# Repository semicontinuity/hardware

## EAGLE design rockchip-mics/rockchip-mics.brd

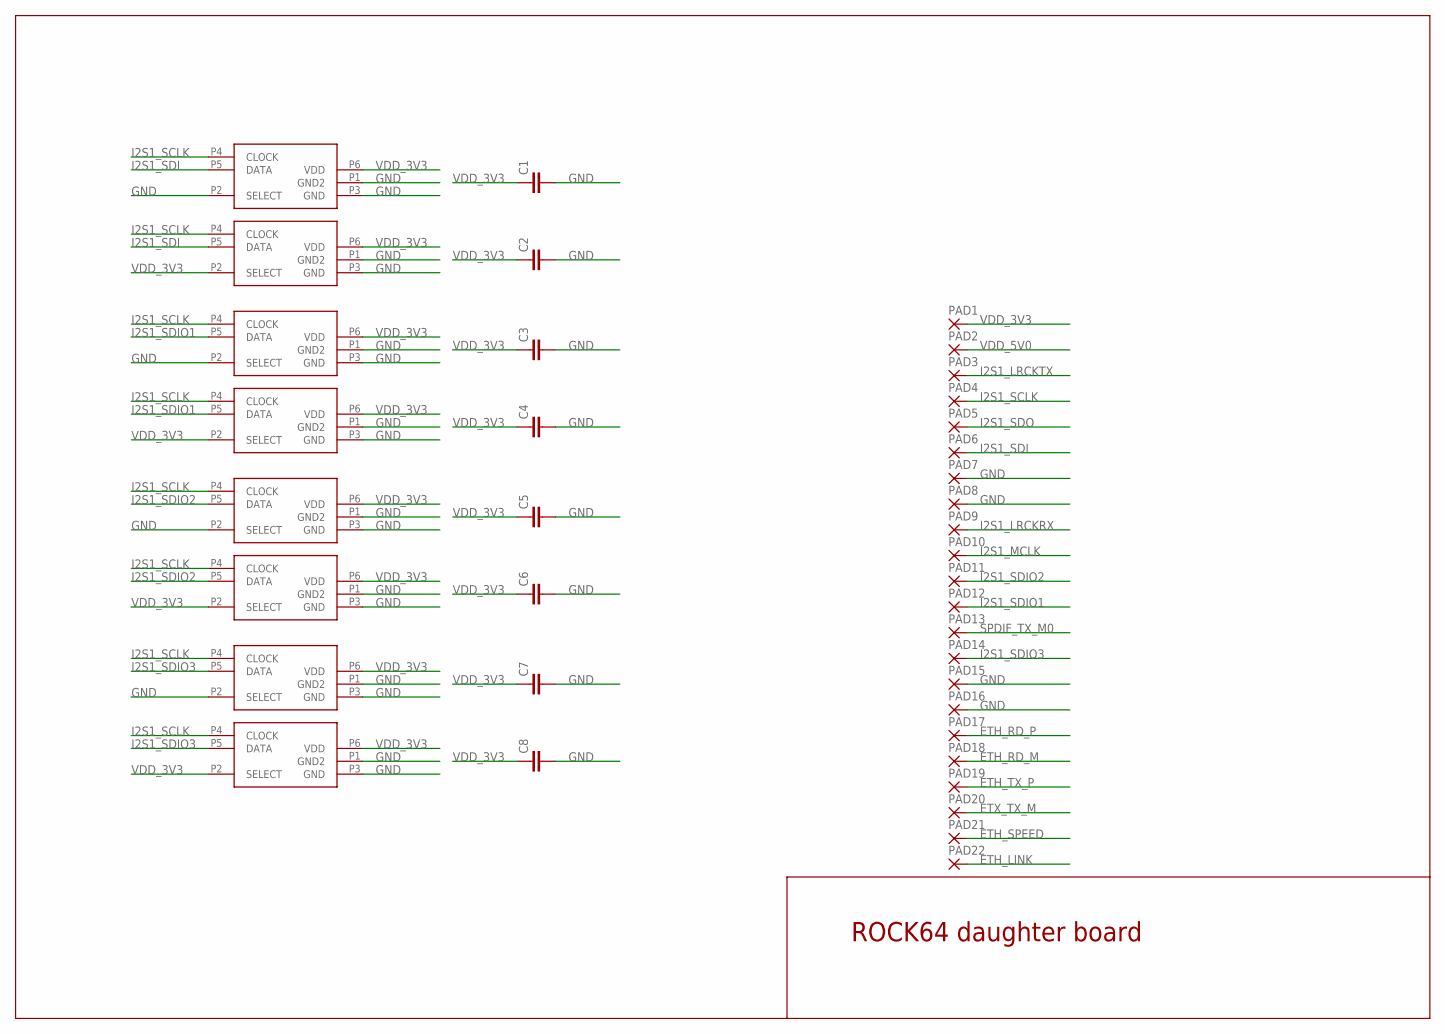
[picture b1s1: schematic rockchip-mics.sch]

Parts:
C1, C2, C3, C4, C5, C6, C7, C8: C-EUC1206; C1206
PAD1, PAD2, PAD3, PAD4, PAD5, PAD6, PAD7, PAD8, PAD9, PAD10, PAD11, PAD12, PAD13, PAD14, PAD15, PAD16, PAD17, PAD18, PAD19, PAD20, PAD21, PAD22: 1,6/0,8
U$1, U$2, U$3, U$4, U$5, U$6, U$7, U$8: SPM0423SMD; SPM0423

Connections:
ETH_LINK: PAD22.1
ETH_RD_M: PAD18.1
ETH_RD_P: PAD17.1
ETH_SPEED: PAD21.1
ETH_TX_P: PAD19.1
ETX_TX_M: PAD20.1
GND: C1.2, C2.2, C3.2, C4.2, C5.2, C6.2, C7.2, C8.2, PAD7.1, PAD8.1, PAD15.1, PAD16.1, U$1.P1 (GND2), U$1.P2 (SELECT), U$1.P3 (GND), U$2.P1 (GND2), U$2.P3 (GND), U$3.P1 (GND2), U$3.P2 (SELECT), U$3.P3 (GND), U$4.P1 (GND2), U$4.P3 (GND), U$5.P1 (GND2), U$5.P2 (SELECT), U$5.P3 (GND), U$6.P1 (GND2), U$6.P3 (GND), U$7.P1 (GND2), U$7.P2 (SELECT), U$7.P3 (GND), U$8.P1 (GND2), U$8.P3 (GND)
I2S1_LRCKRX: PAD9.1
I2S1_LRCKTX: PAD3.1
I2S1_MCLK: PAD10.1
I2S1_SCLK: PAD4.1, U$1.P4 (CLOCK), U$2.P4 (CLOCK), U$3.P4 (CLOCK), U$4.P4 (CLOCK), U$5.P4 (CLOCK), U$6.P4 (CLOCK), U$7.P4 (CLOCK), U$8.P4 (CLOCK)
I2S1_SDI: PAD6.1, U$1.P5 (DATA), U$2.P5 (DATA)
I2S1_SDIO1: PAD12.1, U$3.P5 (DATA), U$4.P5 (DATA)
I2S1_SDIO2: PAD11.1, U$5.P5 (DATA), U$6.P5 (DATA)
I2S1_SDIO3: PAD14.1, U$7.P5 (DATA), U$8.P5 (DATA)
I2S1_SDO: PAD5.1
SPDIF_TX_M0: PAD13.1
VDD_3V3: C1.1, C2.1, C3.1, C4.1, C5.1, C6.1, C7.1, C8.1, PAD1.1, U$1.P6 (VDD), U$2.P2 (SELECT), U$2.P6 (VDD), U$3.P6 (VDD), U$4.P2 (SELECT), U$4.P6 (VDD), U$5.P6 (VDD), U$6.P2 (SELECT), U$6.P6 (VDD), U$7.P6 (VDD), U$8.P2 (SELECT), U$8.P6 (VDD)
VDD_5V0: PAD2.1

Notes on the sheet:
ROCK64 daughter board

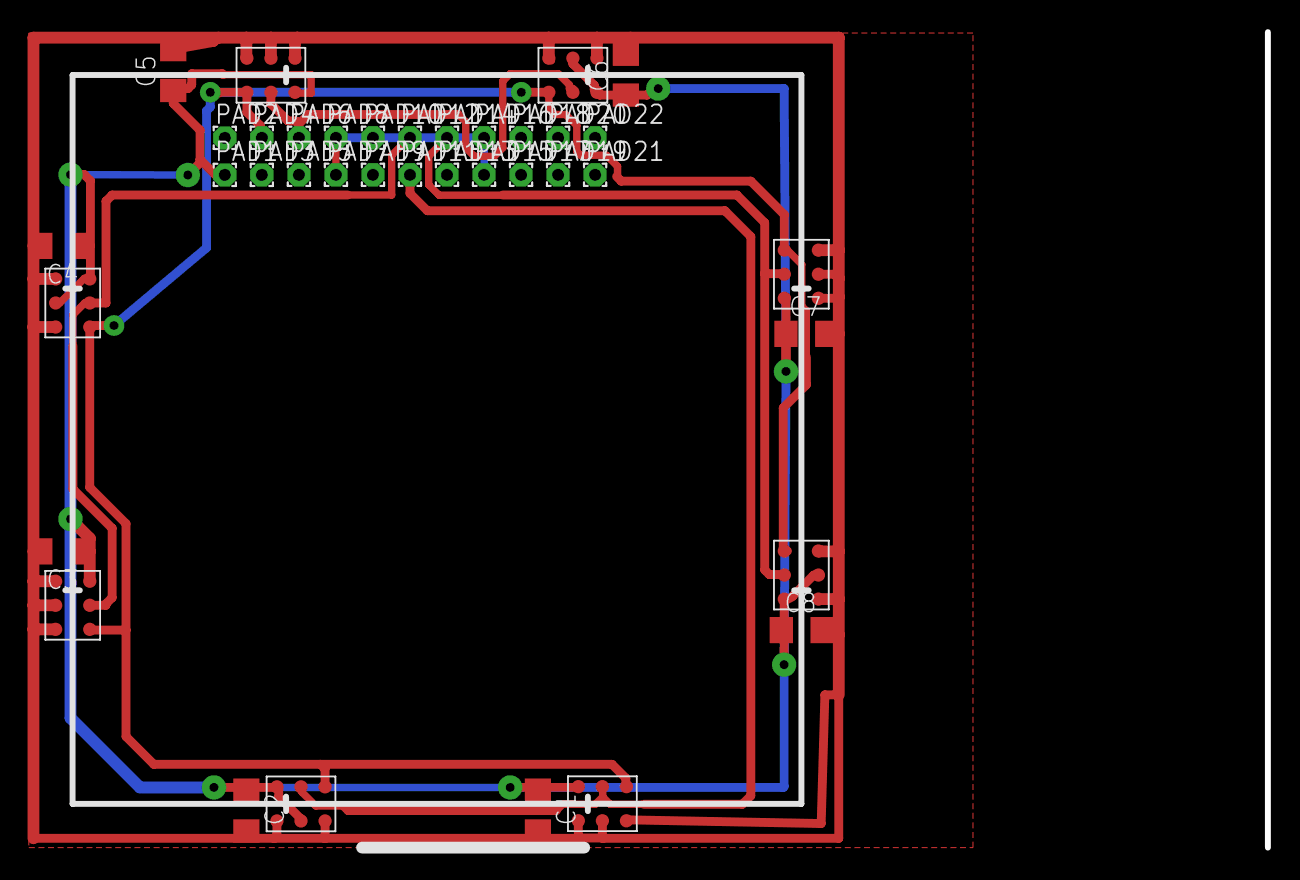
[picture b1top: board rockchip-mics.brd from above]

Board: 2 copper layers, 38 parts (0 on the bottom side), 7 nets.

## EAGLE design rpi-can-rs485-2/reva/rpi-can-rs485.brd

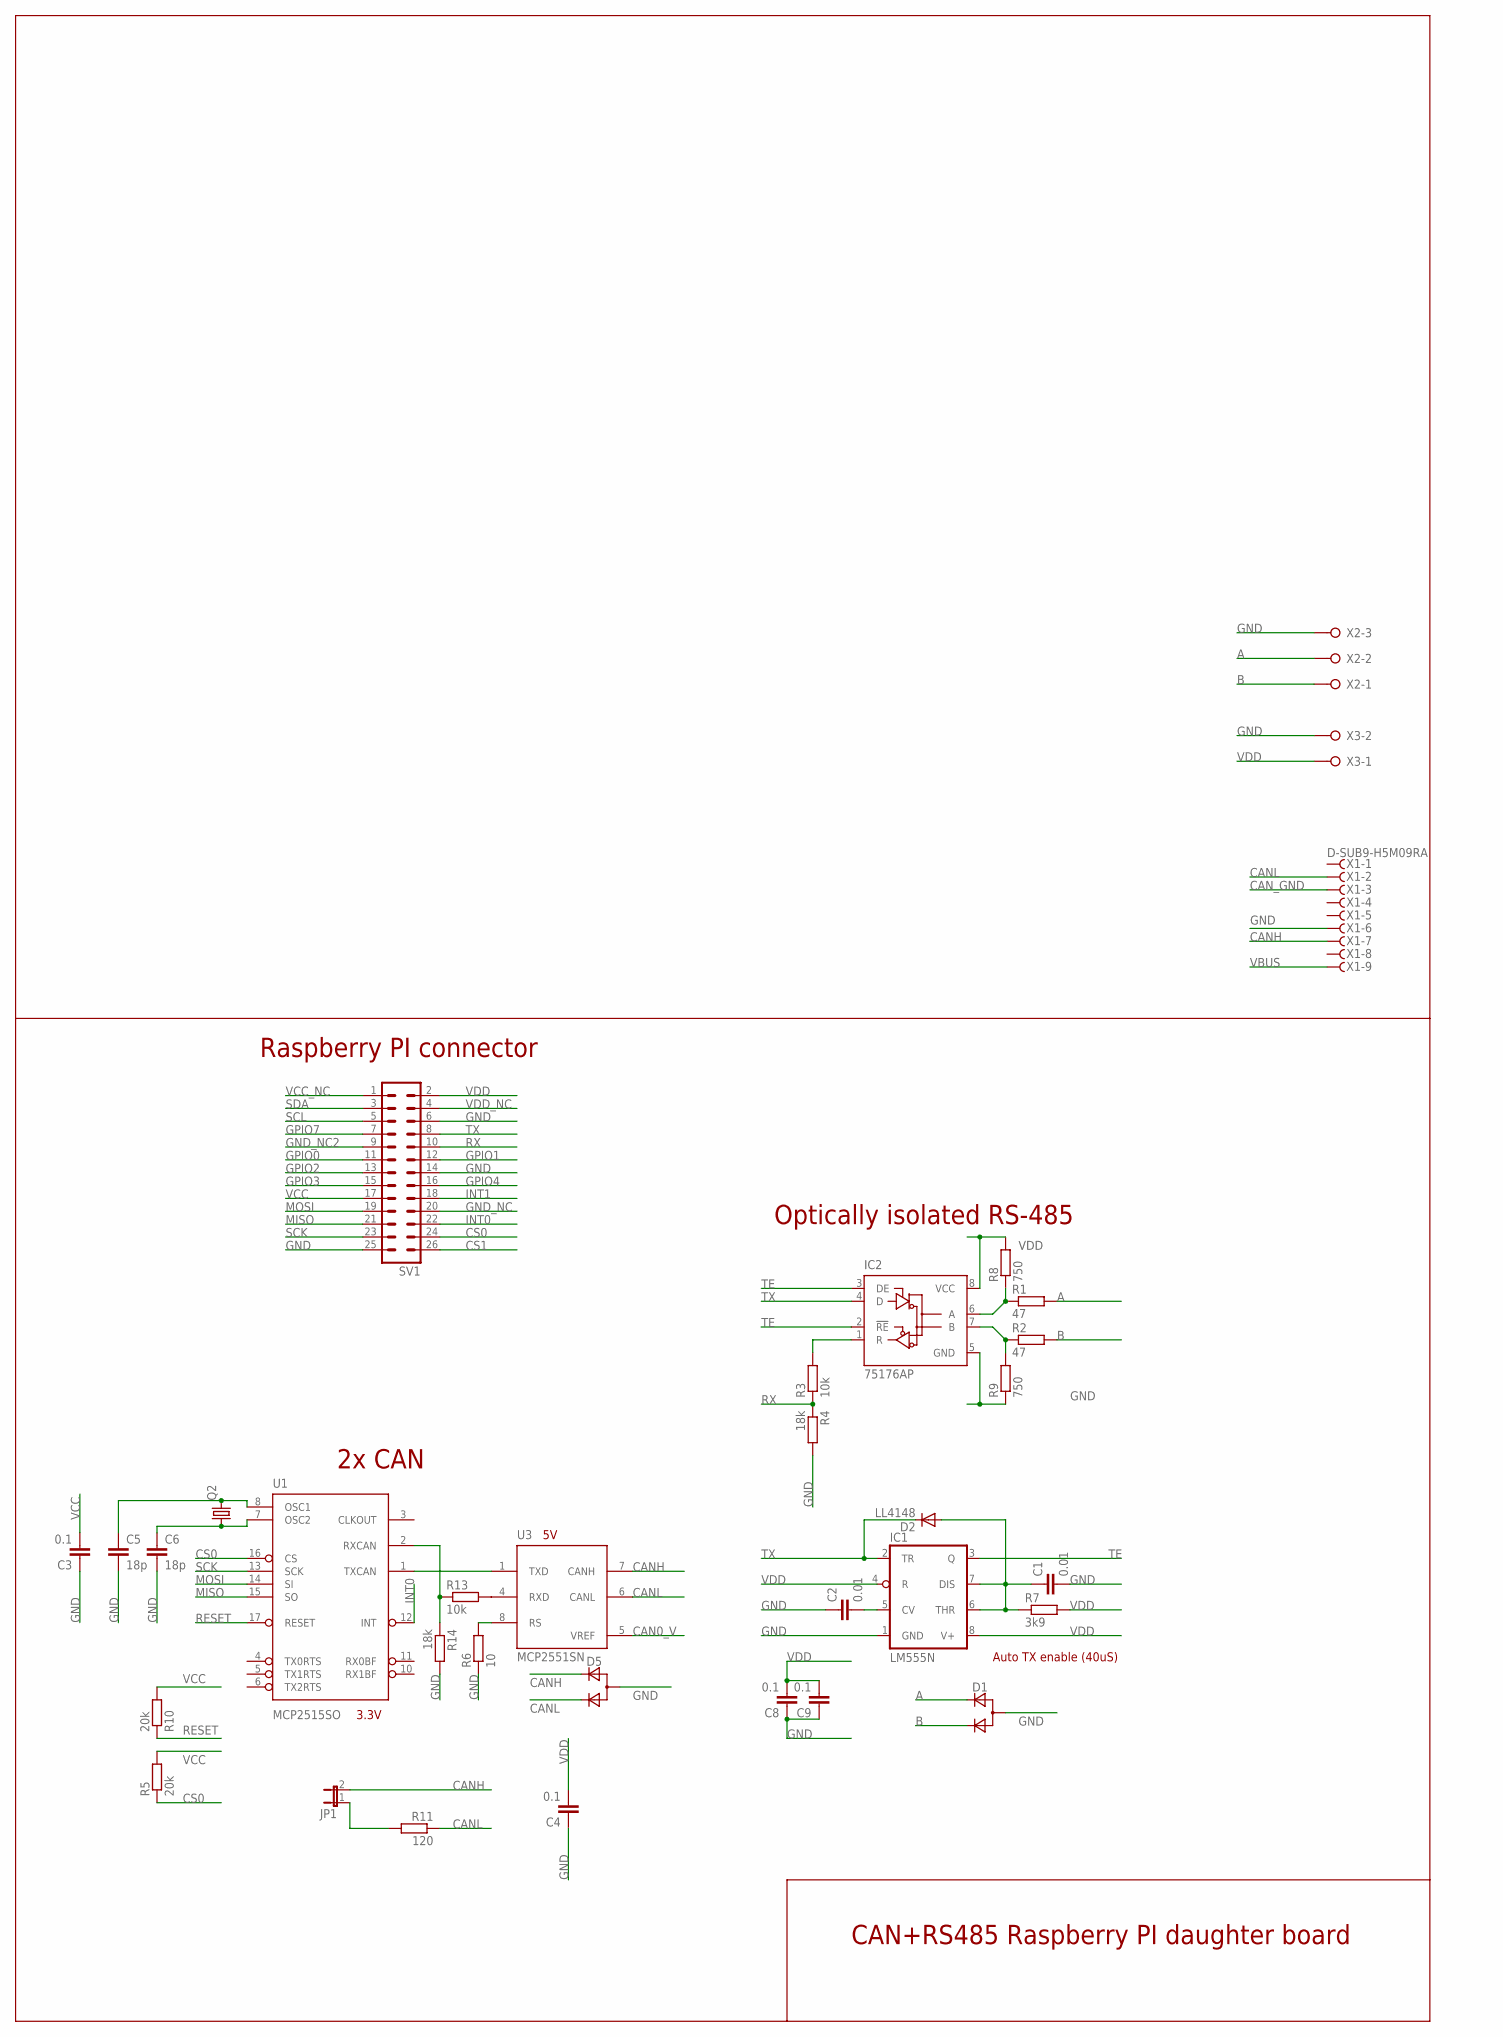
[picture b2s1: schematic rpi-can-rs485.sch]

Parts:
C1, C2: 0.01; C0805
C3, C4, C8, C9: 0.1; C0805
C5, C6: 18p; C0805
D1, D5: D_2CSOT323; SOT323
D2: LL4148; SOD80C
IC1: LM555N; DIL08
IC2: 75176AP; DIL08
JP1: JP1E; JP1
Q2: CRYSTALHC49S; HC49/S
R1, R2: 47; R1206
R3, R13: 10k; R0805
R4, R14: 18k; R0805
R5: 20k; R0603
R6: 10; R0805
R7: 3k9; R0805
R8, R9: 750; R1206
R10: 20k; R0805
R11: 120; R0805
SV1: MA13-2
U1: MCP2515SO; SO-18W
U3: MCP2551SN; SO-08
X1: D-SUB9-H5M09RA; H5M09RA
X2: W237-03P; W237-133
X3: W237-02P; W237-132

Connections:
A: D1.2 (C1), R1.2, X2.2
B: D1.3 (C2), R2.2, X2.1
CAN0_TX: U1.1 (TXCAN), U3.1 (TXD)
CAN0_V: U3.5 (VREF)
CANH: D5.2 (C1), JP1.2, U3.7 (CANH), X1.7
CANL: D5.3 (C2), R11.1, U3.6 (CANL), X1.2
CAN_GND: X1.3
CS0: R5.1, SV1.24, U1.16 (CS)
CS1: SV1.26
GND: C1.2, C2.1, C3.1, C4.1, C5.2, C6.2, C8.1, C9.1, D1.1 (A), D5.1 (A), IC1.1 (GND), IC2.5 (GND), R4.2, R6.1, R9.1, R14.2, SV1.6, SV1.14, SV1.25, U1.9 (VSS), U3.2 (VSS), X1.6, X2.3, X3.2
GND_NC: SV1.20
GND_NC2: SV1.9
GPIO0: SV1.11
GPIO1: SV1.12
GPIO2: SV1.13
GPIO3: SV1.15
GPIO4: SV1.16
GPIO7: SV1.7
INT0: SV1.22, U1.12 (INT)
INT1: SV1.18
MISO: SV1.21, U1.15 (SO)
MOSI: SV1.19, U1.14 (SI)
unnamed: C6.1, Q2.1, U1.7 (OSC2)
unnamed: C1.1, D2.A, IC1.6 (THR), IC1.7 (DIS), R7.1
unnamed: IC2.7 (B), R2.1, R9.2
unnamed: IC2.6 (A), R1.1, R8.1
unnamed: C2.2, IC1.5 (CV)
unnamed: C5.1, Q2.2, U1.8 (OSC1)
unnamed: R6.2, U3.8 (RS)
unnamed: IC2.1 (R), R3.2
unnamed: JP1.1, R11.2
unnamed: R13.2, U3.4 (RXD)
unnamed: R13.1, R14.1, U1.2 (RXCAN)
RESET: R10.1, U1.17 (RESET)
RX: R3.1, R4.1, SV1.10
SCK: SV1.23, U1.13 (SCK)
SCL: SV1.5
SDA: SV1.3
TE: IC1.3 (Q), IC2.2 (!RE), IC2.3 (DE)
TX: D2.C, IC1.2 (TR), IC2.4 (D), SV1.8
VBUS: X1.9
VCC: C3.2, R5.2, R10.2, SV1.17, U1.18 (VDD)
VCC_NC: SV1.1
VDD: C4.2, C8.2, C9.2, IC1.4 (R), IC1.8 (V+), IC2.8 (VCC), R7.2, R8.2, SV1.2, U3.3 (VDD), X3.1
VDD_NC: SV1.4

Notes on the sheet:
Raspberry PI connector
2x CAN
Optically isolated RS-485
Auto TX enable (40uS)
CAN+RS485 Raspberry PI daughter board
3.3V

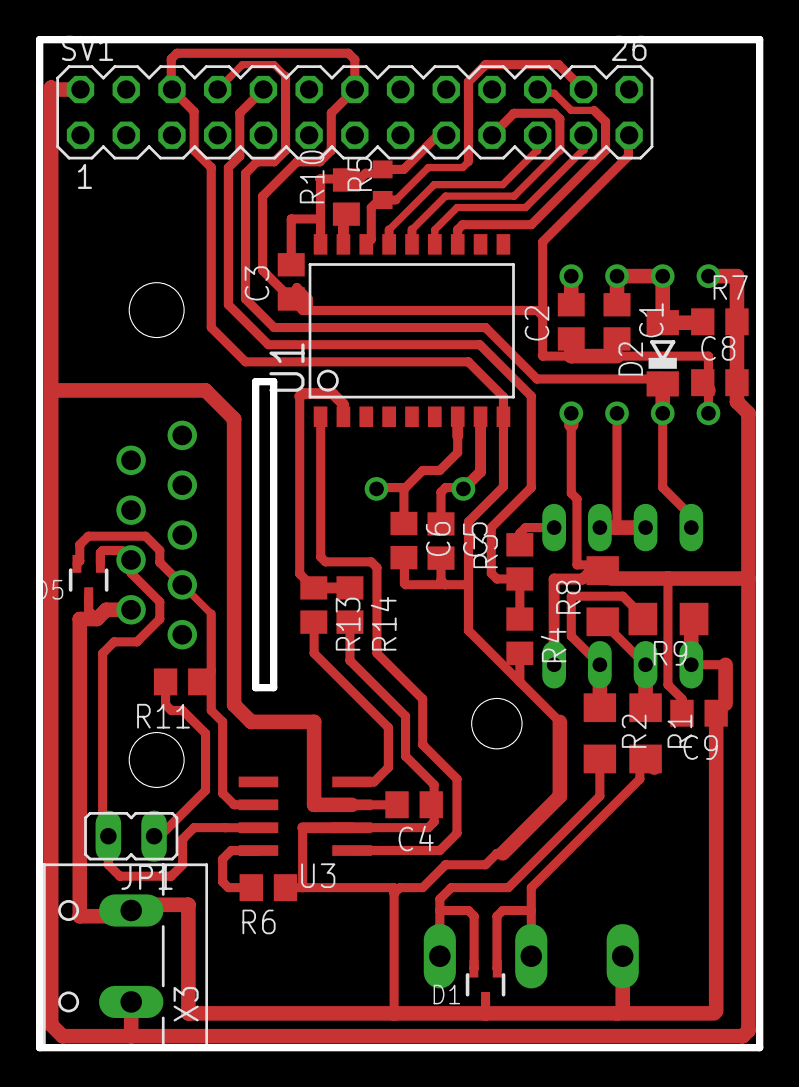
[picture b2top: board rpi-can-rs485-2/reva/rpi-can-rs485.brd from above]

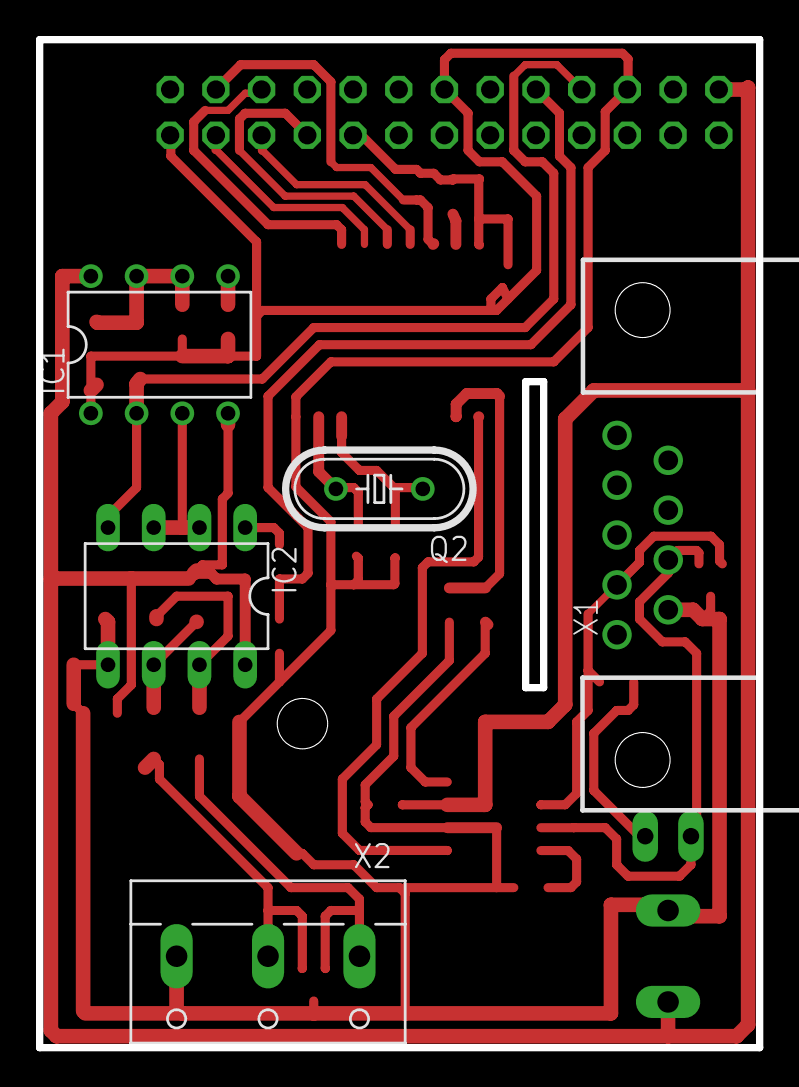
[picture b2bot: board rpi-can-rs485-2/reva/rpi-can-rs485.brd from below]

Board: 2 copper layers, 40.0 x 56.0 mm, 34 parts (5 on the bottom side), 28 nets.

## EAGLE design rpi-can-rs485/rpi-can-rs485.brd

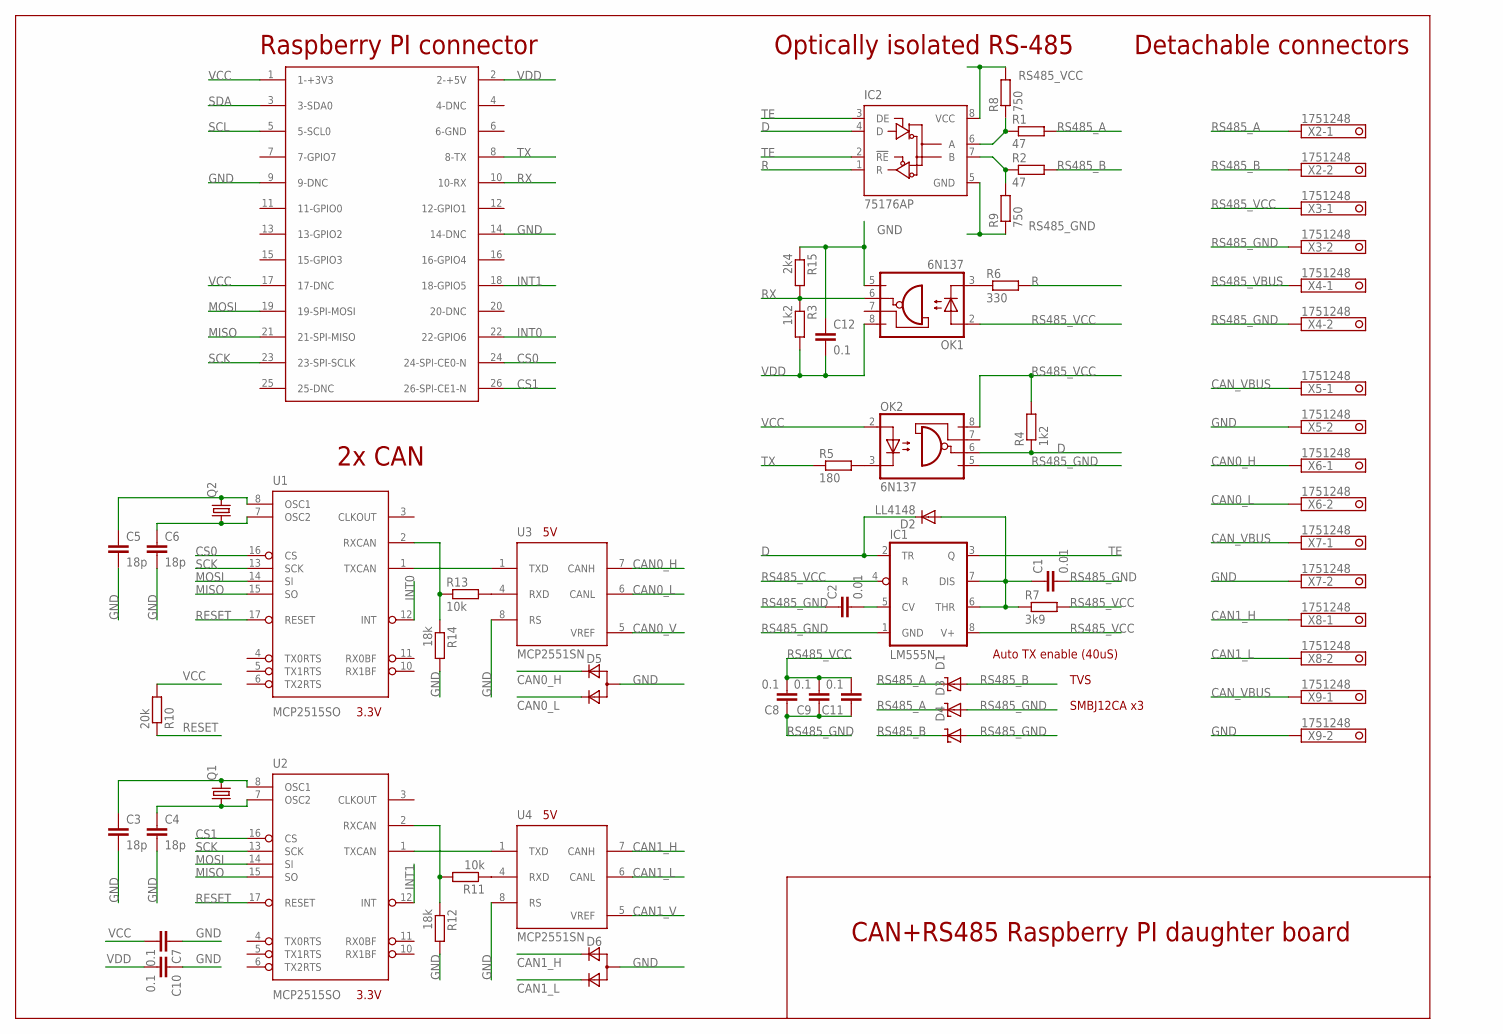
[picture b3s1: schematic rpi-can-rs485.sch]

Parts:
C1, C2: 0.01; C0805
C3, C4, C5, C6: 18p; C0805
C7, C11, C12: 0.1; C1206
C8, C9, C10: 0.1; C0805
D1, D3, D4: SUPPRESSOR-SMBJ; SMBJ
D2: LL4148; SOD80C
D5, D6: D_2CSOT323; SOT323
IC1: LM555N; DIL08
IC2: 75176AP; DIL08
OK1, OK2: 6N137; DIL08
Q1, Q2: CRYSTALHC49S; HC49/S
R1, R2: 47; R1206
R3, R4: 1k2; R0805
R5: 180; R0805
R6: 330; R0805
R7: 3k9; R0805
R8, R9: 750; R1206
R10: 20k; R0805
R11, R13: 10k; R0805
R12, R14: 18k; R0805
R15: 2k4; R0805
U1, U2: MCP2515SO; SO-18W
U3, U4: MCP2551SN; SO-08
U$1: RASPBERRY-PI
X2, X3, X4, X5, X6, X7, X8, X9: 1751248

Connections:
CAN0_H: D5.2 (C1), U3.7 (CANH), X6.1
CAN0_L: D5.3 (C2), U3.6 (CANL), X6.2
CAN0_TX: U1.1 (TXCAN), U3.1 (TXD)
CAN0_V: U3.5 (VREF)
CAN1_H: D6.2 (C1), U4.7 (CANH), X8.1
CAN1_L: D6.3 (C2), U4.6 (CANL), X8.2
CAN1_TX: U2.1 (TXCAN), U4.1 (TXD)
CAN1_V: U4.5 (VREF)
CAN_VBUS: X5.1, X7.1, X9.1
CS0: U1.16 (CS), U$1.24 (24-SPI-CE0-N)
CS1: U2.16 (CS), U$1.26 (26-SPI-CE1-N)
D: D2.C, IC1.2 (TR), IC2.4 (D), OK2.6 (VO), R4.1
GND: C3.2, C4.2, C5.2, C6.2, C7.1, C10.1, C12.1, D5.1 (A), D6.1 (A), OK1.5 (GND), R12.2, R14.2, R15.1, U1.9 (VSS), U2.9 (VSS), U3.2 (VSS), U3.8 (RS), U4.2 (VSS), U4.8 (RS), U$1.9 (9-DNC), U$1.14 (14-DNC), X5.2, X7.2, X9.2
INT0: U1.12 (INT), U$1.22 (22-GPIO6)
INT1: U2.12 (INT), U$1.18 (18-GPIO5)
MISO: U1.15 (SO), U2.15 (SO), U$1.21 (21-SPI-MISO)
MOSI: U1.14 (SI), U2.14 (SI), U$1.19 (19-SPI-MOSI)
unnamed: C6.1, Q2.1, U1.7 (OSC2)
unnamed: C1.1, D2.A, IC1.6 (THR), IC1.7 (DIS), R7.1
unnamed: IC2.7 (B), R2.1, R9.2
unnamed: IC2.6 (A), R1.1, R8.1
unnamed: C2.2, IC1.5 (CV)
unnamed: C5.1, Q2.2, U1.8 (OSC1)
unnamed: OK2.3 (C), R5.2
unnamed: OK1.3 (C), R6.1
unnamed: R11.1, U4.4 (RXD)
unnamed: R13.2, U3.4 (RXD)
unnamed: C3.1, Q1.2, U2.8 (OSC1)
unnamed: C4.1, Q1.1, U2.7 (OSC2)
unnamed: R13.1, R14.1, U1.2 (RXCAN)
unnamed: R11.2, R12.1, U2.2 (RXCAN)
R: IC2.1 (R), R6.2
RESET: R10.1, U1.17 (RESET), U2.17 (RESET)
RS485_A: D1.C, D3.C, R1.2, X2.1
RS485_B: D1.A, D4.C, R2.2, X2.2
RS485_GND: C1.2, C2.1, C8.1, C9.1, C11.1, D3.A, D4.A, IC1.1 (GND), IC2.5 (GND), OK2.5 (GND), R9.1, X3.2, X4.2
RS485_VBUS: X4.1
RS485_VCC: C8.2, C9.2, C11.2, IC1.4 (R), IC1.8 (V+), IC2.8 (VCC), OK1.2 (A), OK2.8 (VCC), R4.2, R7.2, R8.2, X3.1
RX: OK1.6 (VO), R3.1, R15.2, U$1.10 (10-RX)
SCK: U1.13 (SCK), U2.13 (SCK), U$1.23 (23-SPI-SCLK)
SCL: U$1.5 (5-SCL0)
SDA: U$1.3 (3-SDA0)
TE: IC1.3 (Q), IC2.2 (!RE), IC2.3 (DE)
TX: R5.1, U$1.8 (8-TX)
VCC: C7.2, OK2.2 (A), R10.2, U1.18 (VDD), U2.18 (VDD), U$1.1 (1-+3V3), U$1.17 (17-DNC)
VDD: C10.2, C12.2, OK1.8 (VCC), R3.2, U3.3 (VDD), U4.3 (VDD), U$1.2 (2-+5V)

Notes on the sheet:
Raspberry PI connector
2x CAN
Optically isolated RS-485
TVS
SMBJ12CA x3
Auto TX enable (40uS)
Detachable connectors
CAN+RS485 Raspberry PI daughter board
3.3V

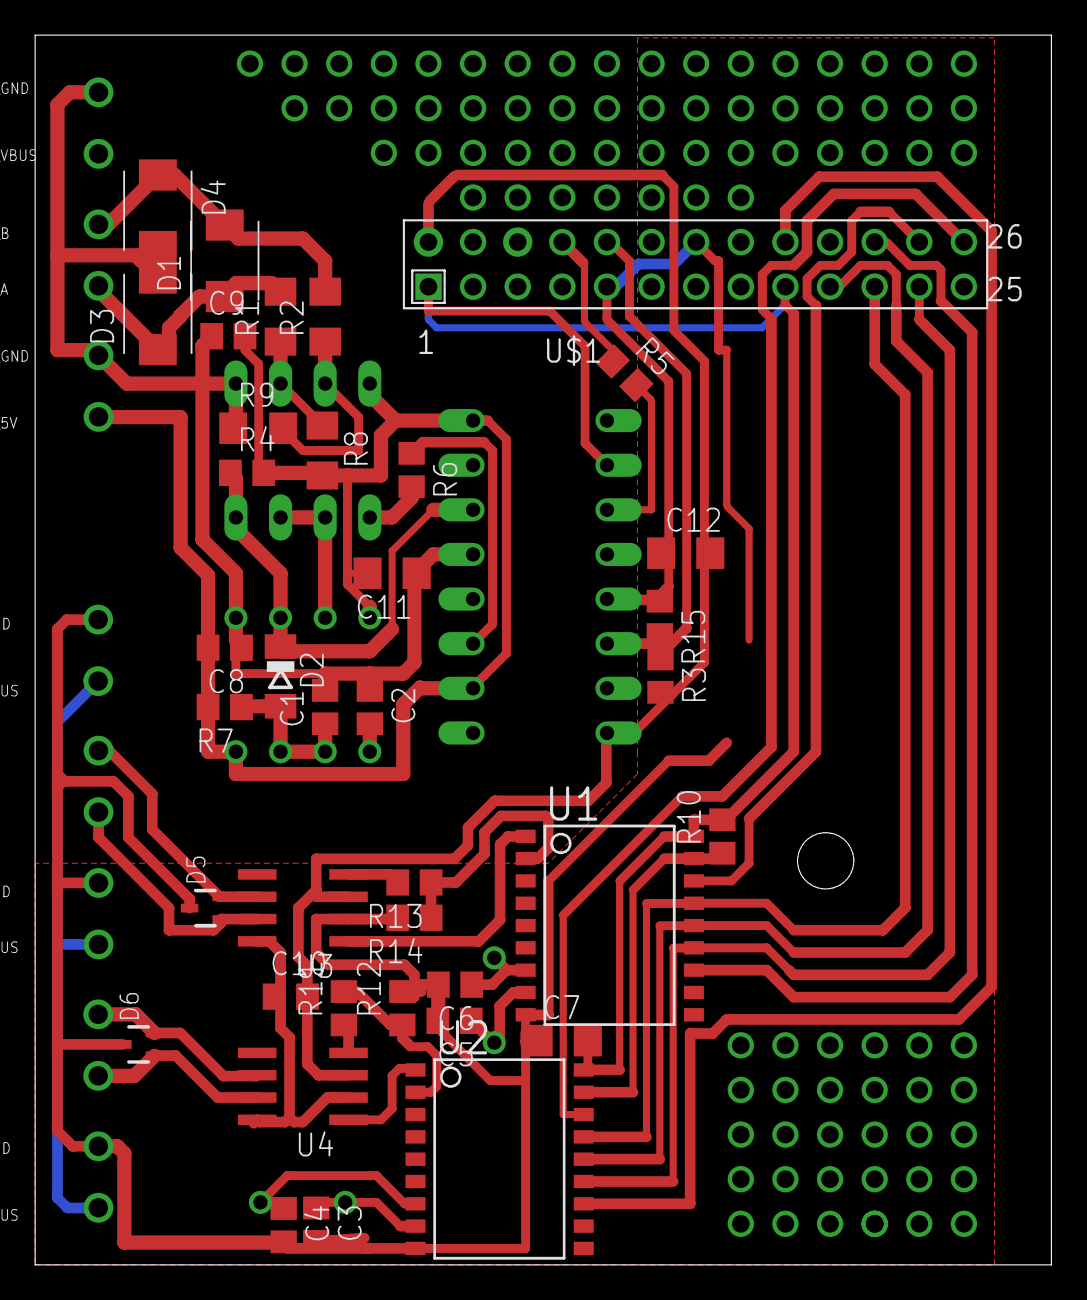
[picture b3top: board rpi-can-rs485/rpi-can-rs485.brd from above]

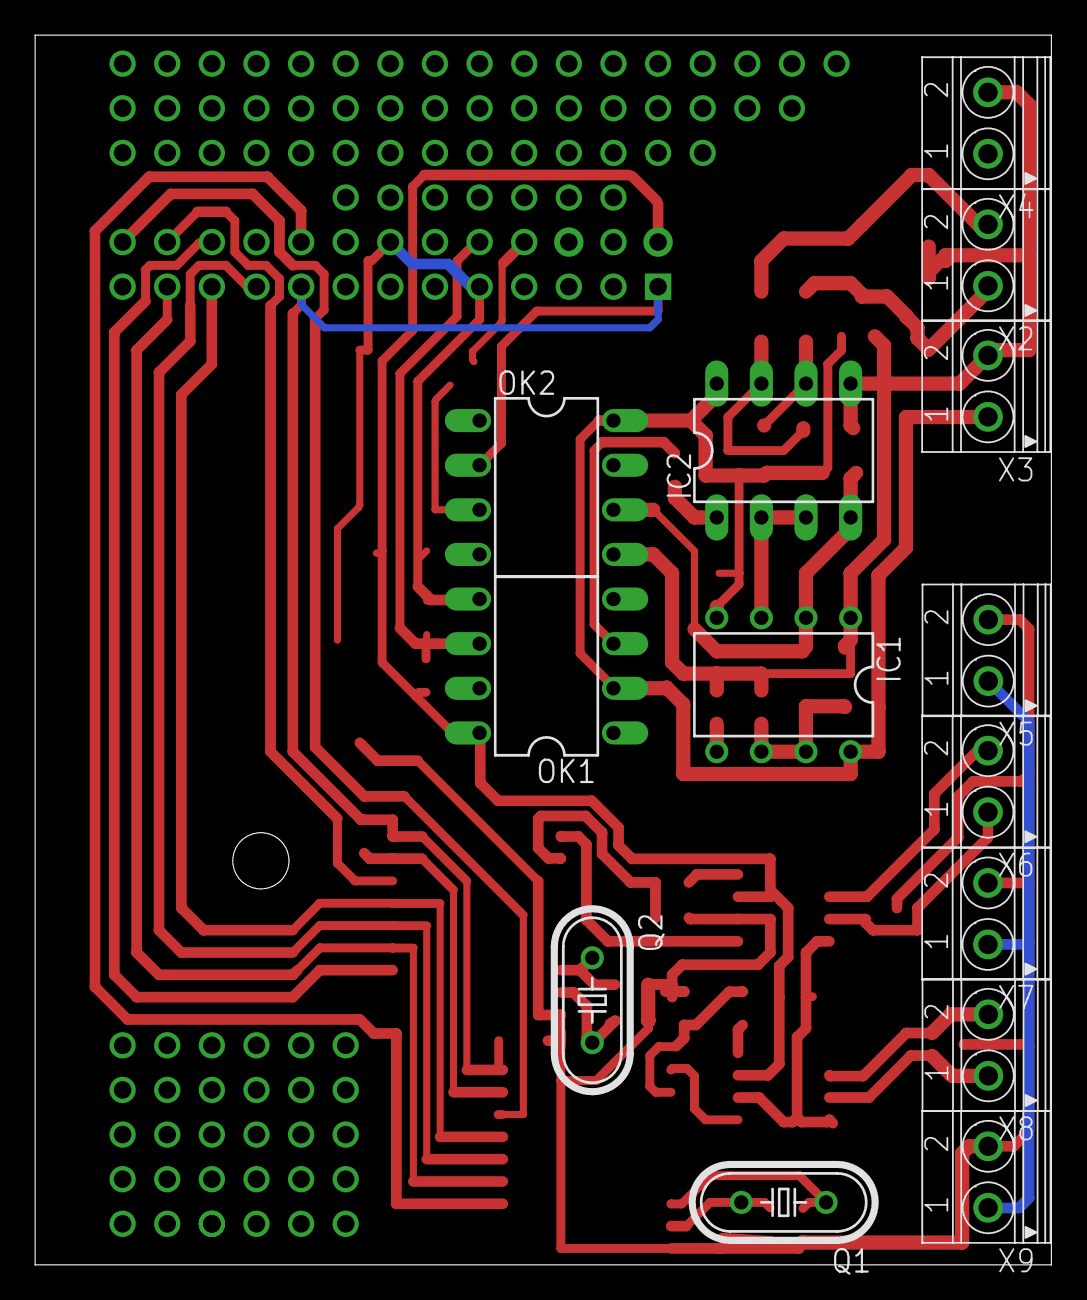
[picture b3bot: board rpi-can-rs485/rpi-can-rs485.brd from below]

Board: 2 copper layers, 57.9 x 70.0 mm, 52 parts (14 on the bottom side), 41 nets.

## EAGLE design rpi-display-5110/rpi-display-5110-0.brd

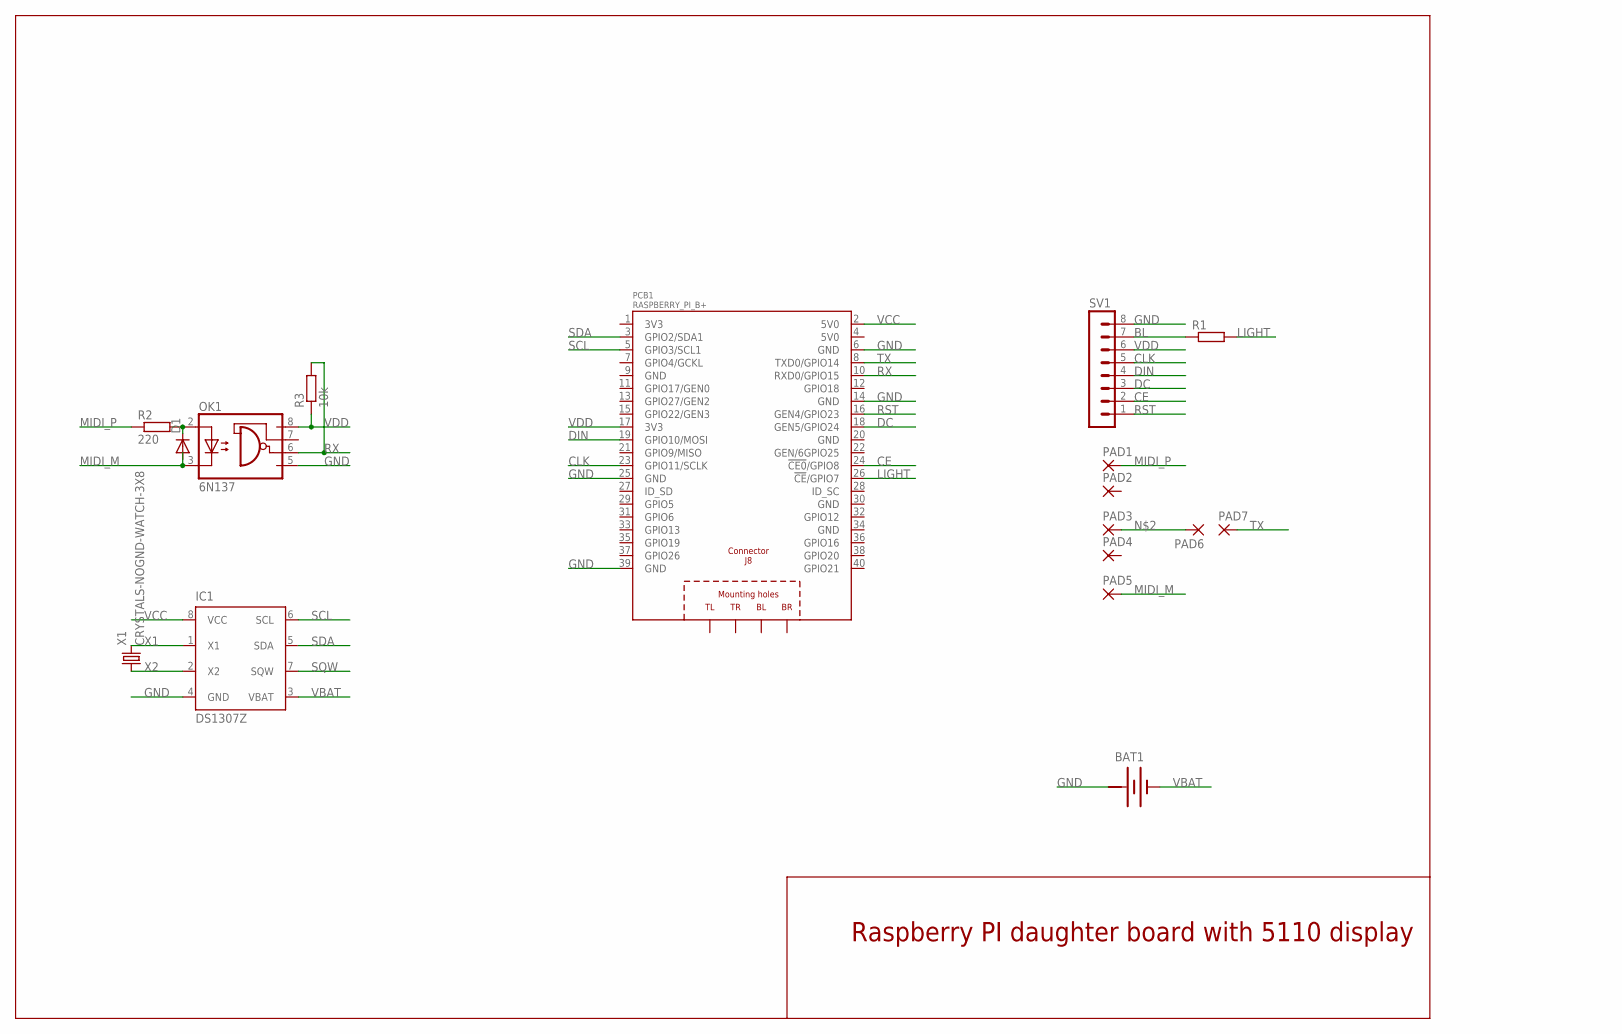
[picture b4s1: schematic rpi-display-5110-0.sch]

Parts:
BAT1: BATTERY
D1: DIODE-MINIMELF; MINIMELF
IC1: DS1307Z; SOIC8
OK1: 6N137; DIL08
PAD1, PAD2, PAD3, PAD4, PAD5, PAD6, PAD7: 1,6/0,8
PCB1: RASPBERRY_PI_B+
R1: R-EU_R0805; R0805
R2: 220; R0805
R3: 10k; R0805
SV1: MA08-1
X1: CRYSTALS-NOGND-WATCH-3X8; WATCH-3X8

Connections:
+: BAT1.+@1 (+)
BL: R1.1, SV1.7
CE: PCB1.24 (!CE0!/GPIO8), SV1.2
CLK: PCB1.23 (GPIO11/SCLK), SV1.5
DC: PCB1.18 (GEN5/GPIO24), SV1.3
DIN: PCB1.19 (GPIO10/MOSI), SV1.4
GND: BAT1.+, IC1.4 (GND), OK1.5 (GND), PCB1.6 (GND), PCB1.14 (GND), PCB1.25 (GND), PCB1.39 (GND), SV1.8
LIGHT: PCB1.26 (!CE!/GPIO7), R1.2
MIDI_M: OK1.3 (C), PAD5.1
MIDI_P: PAD1.1, R2.1
unnamed: D1.C, OK1.2 (A), R2.2
unnamed: PAD3.1, PAD6.1
RST: PCB1.16 (GEN4/GPIO23), SV1.1
RX: OK1.6 (VO), PCB1.10 (RXD0/GPIO15), R3.2
SCL: IC1.6 (SCL), PCB1.5 (GPIO3/SCL1)
SDA: IC1.5 (SDA), PCB1.3 (GPIO2/SDA1)
SQW: IC1.7 (SQW)
TX: PAD7.1, PCB1.8 (TXD0/GPIO14)
VBAT: BAT1.-, IC1.3 (VBAT)
VCC: IC1.8 (VCC), PCB1.2 (5V0)
VDD: OK1.8 (VCC), PCB1.17 (3V3), R3.1, SV1.6
X1: IC1.1 (X1), X1.2
X2: IC1.2 (X2), X1.1

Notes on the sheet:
Raspberry PI daughter board with 5110 display

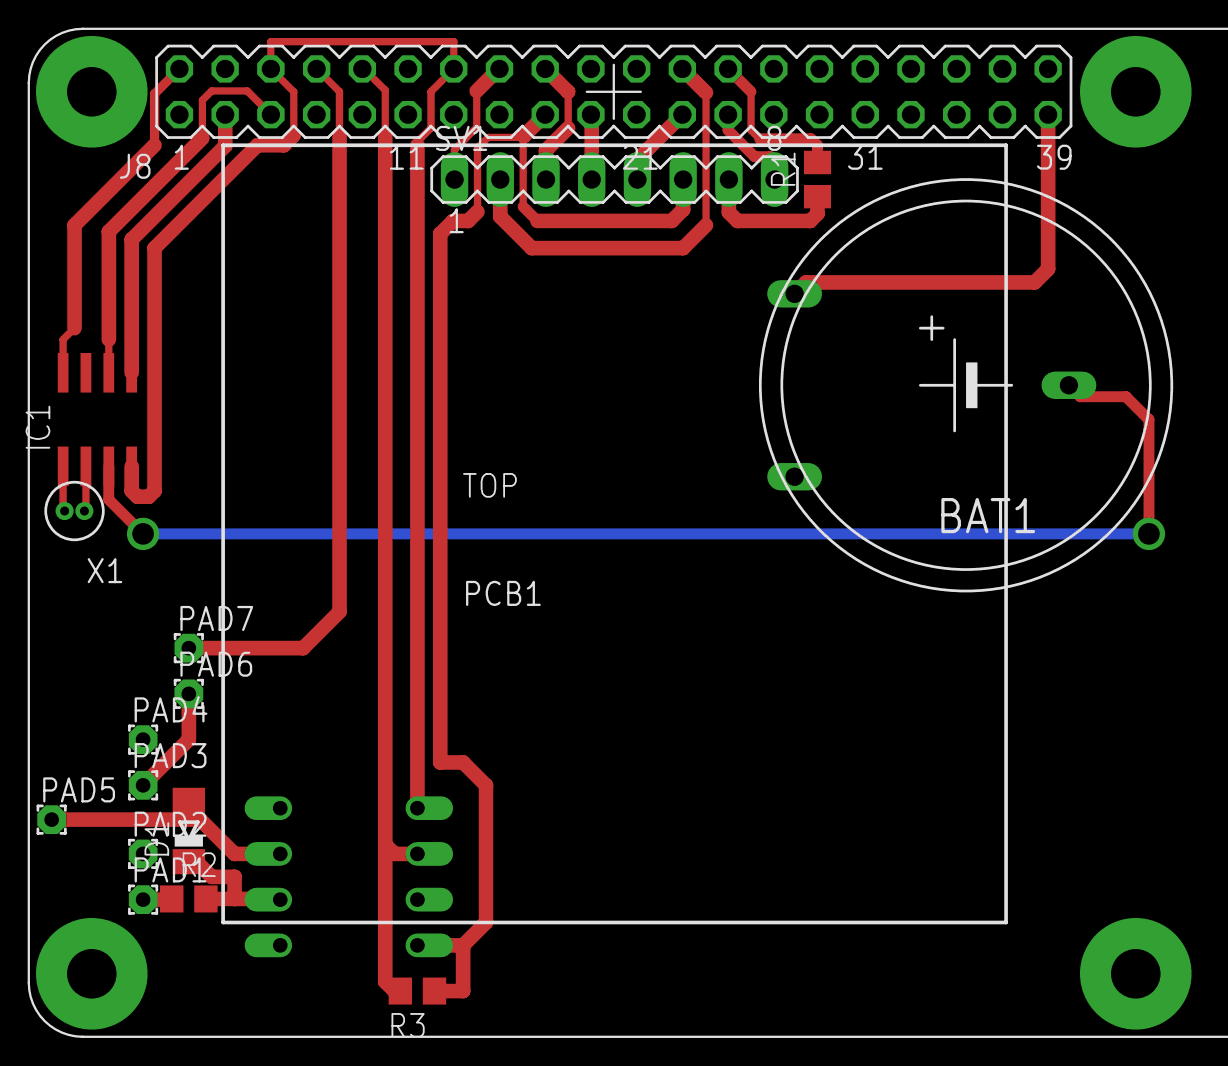
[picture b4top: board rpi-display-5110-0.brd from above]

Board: 2 copper layers, 17 parts (1 on the bottom side), 21 nets.

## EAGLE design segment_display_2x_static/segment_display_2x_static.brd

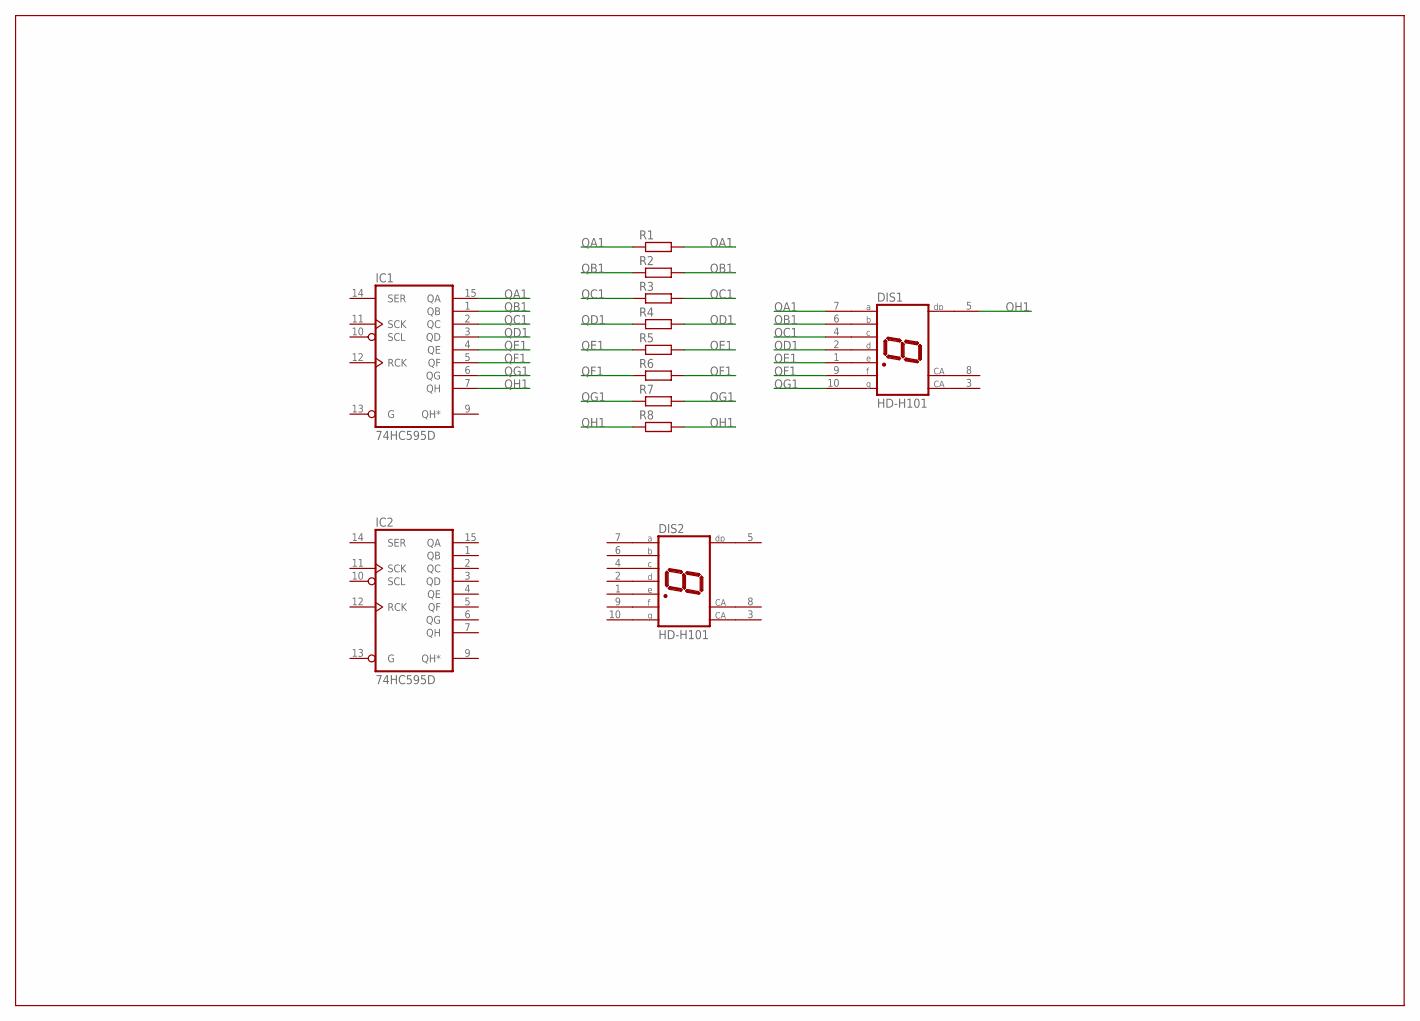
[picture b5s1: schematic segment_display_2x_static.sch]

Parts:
DIS1, DIS2: HD-H101; HDSP-M
IC1, IC2: 74HC595D; SO16
R1, R2, R3, R4, R5, R6, R7, R8: R-EU_R0603; R0603

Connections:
GND: IC1.8 (GND), IC2.8 (GND)
OA1: DIS1.7 (A), R1.2
OB1: DIS1.6 (B), R2.2
OC1: DIS1.4 (C), R3.2
OD1: DIS1.2 (D), R4.2
OE1: DIS1.1 (E), R5.2
OF1: DIS1.9 (F), R6.2
OG1: DIS1.10 (G), R7.2
OH1: DIS1.5 (DP), R8.2
QA1: IC1.15 (QA), R1.1
QB1: IC1.1 (QB), R2.1
QC1: IC1.2 (QC), R3.1
QD1: IC1.3 (QD), R4.1
QE1: IC1.4 (QE), R5.1
QF1: IC1.5 (QF), R6.1
QG1: IC1.6 (QG), R7.1
QH1: IC1.7 (QH), R8.1
VCC: IC1.16 (VCC), IC2.16 (VCC)

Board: 2 copper layers, 12 parts (2 on the bottom side), 18 nets, no tracks yet.
